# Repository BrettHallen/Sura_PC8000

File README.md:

# СУРА ПК8000<br>SURA PC8000
Projects for the Soviet "inspired by MSX" computer called the СУРА ПК8000.<br>

Also known as the ВЕСТА (Vesta) and ХОББИ (Hobby).

## YouTube Videos
- [Part 1: First look](https://youtu.be/wWDCWSeaxUg)
- [Part 2: New power supply test](https://youtu.be/me7krCPeANg)

## Useful Links
Mostly in Russian - I use Chrome which has a handy "Translate to English" right-click option.<br>

- [Wikipedia](https://ru.wikipedia.org/wiki/ПК8000)
- [PK8000 site](https://pk8000.narod.ru/)

## [Video Converter](/HDMI_Video_Adaptor_EN)
Work in progress - a video converter designed for Soviet computers.<br>
My only contribution is translating the Python script from Russian to English.<br>

## [PSU Replacement](/Sura_PSU)
Work in progress - my Sura's original 220VAC power supply is very unhappy.  This is my attempt at a simpler, universal (12VDC input) replacement.<br>

I have tested the original Rev. A design ... it works ... but I need to make some tweaks so there will be a Rev. B coming soon.<br>

The original PSU outputs the following via X11 interface:
|X11 port|Voltage|
|--------|-------|
| X11-5  | +5V   |
| X11-6  | +5V   |
| X11-8  | -12V  |
| X11-10 | 0V    |
| X11-12 | +12V  |
| X11-24 | +12V  |
| X11-25 | +5V   |
| X11-26 | +5V   |
| X11-27 | 0V    |

## [Documentation](/Documentation)
Original documentation in Russian, plus any details I've created of my own.<br>
Documentation was sourced from the [PK8000 site](https://pk8000.narod.ru/).

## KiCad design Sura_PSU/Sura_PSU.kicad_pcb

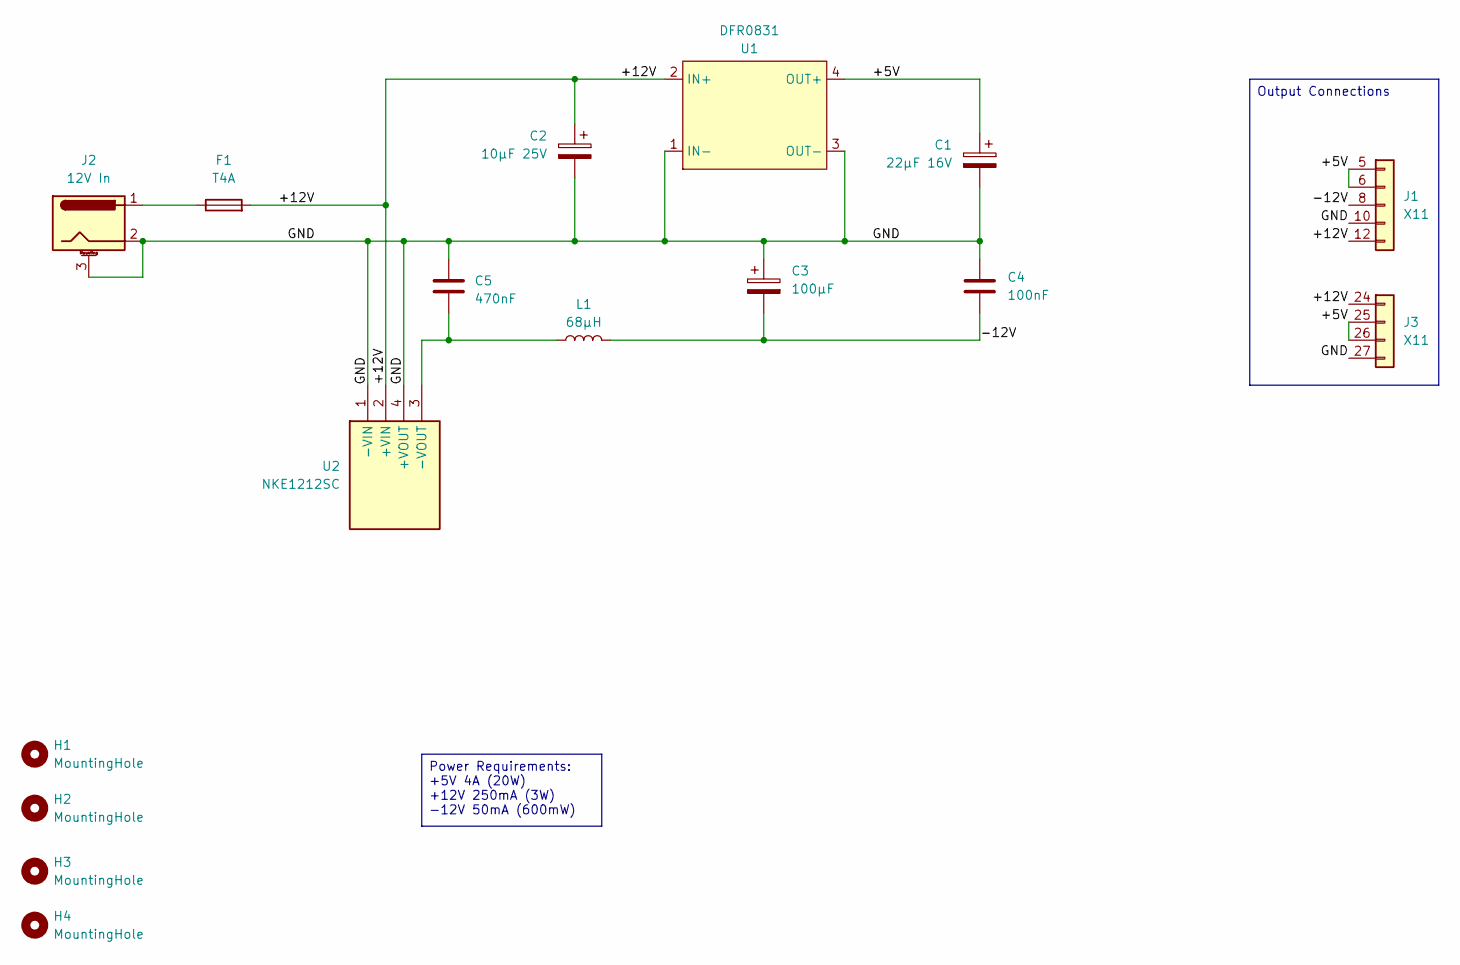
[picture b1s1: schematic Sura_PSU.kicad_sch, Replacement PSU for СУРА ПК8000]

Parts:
C1: 22µF 16V; CP_Radial_D5.0mm_P2.50mm
C2: 10µF 25V; CP_Radial_D5.0mm_P2.50mm
C3: 100µF; CP_Radial_D5.0mm_P2.50mm
C4: 100nF; C_Disc_D3.4mm_W2.1mm_P2.50mm
C5: 470nF; C_Disc_D3.4mm_W2.1mm_P2.50mm
F1: T4A; Fuseholder_Clip-5x20mm_Littelfuse_111_Inline_P20.00x5.00mm_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
H1, H2, H3, H4: MountingHole; MountingHole_3.2mm_M3
J1: X11; PinHeader_1x05_P2.54mm_Vertical
J2: 12V In; 694106301002
J3: X11; PinHeader_1x04_P2.54mm_Vertical
L1: 68µH; 22R683C
U1: DFR0831
U2: NKE1212SC; Manufacturer_Part_Number NKE1212SC

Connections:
/+5V: C1.1, J1.5 (Pin_1), J1.6 (Pin_2), J3.25 (Pin_2), J3.26 (Pin_3), U1.4 (OUT+)
/+12V: C2.1, F1.2, J1.12 (Pin_5), J3.24 (Pin_1), U1.2 (IN+), U2.2 (+VIN)
/-12V: C3.2, C4.2, J1.8 (Pin_3), L1.2
/GND: C1.2, C2.2, C3.1, C4.1, C5.2, J1.10 (Pin_4), J2.2, J2.3 (MountPin), J3.27 (Pin_4), U1.1 (IN-), U1.3 (OUT-), U2.1 (-VIN), U2.4 (+VOUT)
unnamed: F1.1, J2.1
unnamed: C5.1, L1.1, U2.3 (-VOUT)

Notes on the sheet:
Power Requirements: +5V 4A (20W) +12V 250mA (3W) -12V 50mA (600mW)
Output Connections

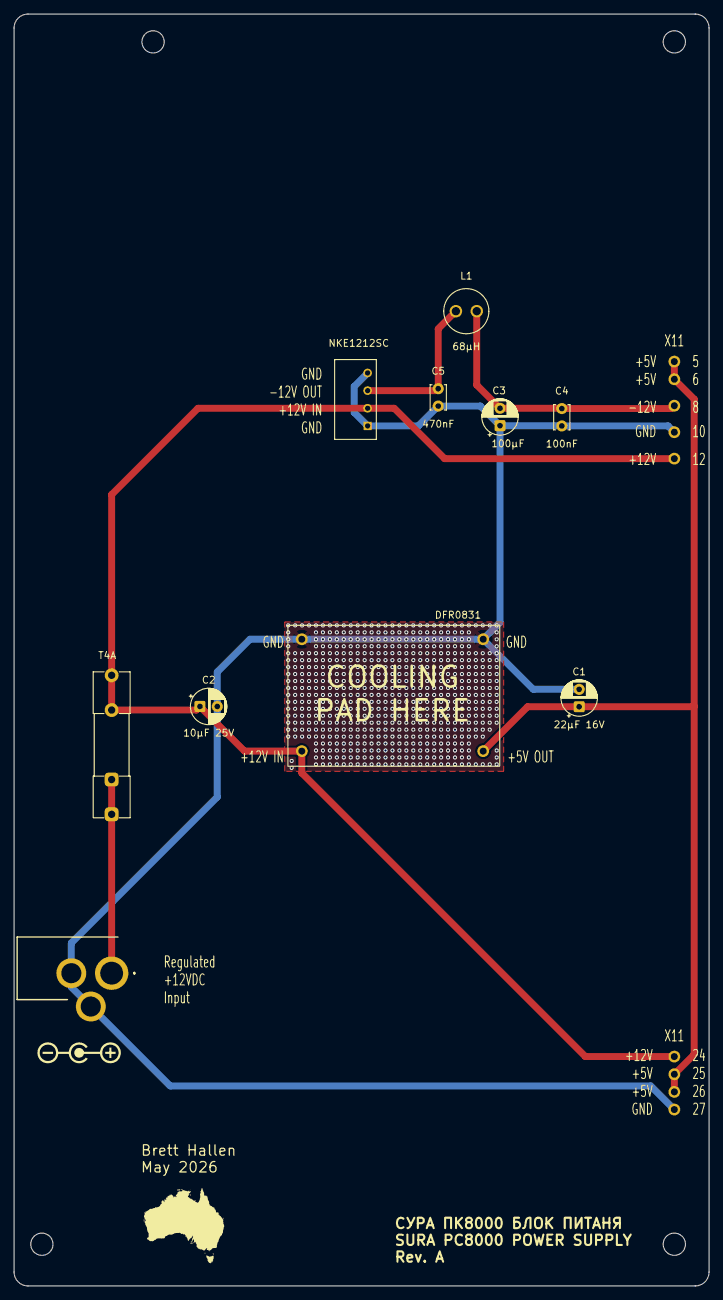
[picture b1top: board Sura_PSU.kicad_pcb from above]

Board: 2 copper layers, 100.0 x 183.0 mm, 16 parts (0 on the bottom side), 6 nets.

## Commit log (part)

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2026-05-13 "бидео" to "видео" (doh)
2026-05-13 Initial design started
2026-05-13 Initial RU->EN translation, untested
2026-05-14 Initial commit (to be tested)
2026-05-14 Updated design (swapped 5V regulator)
